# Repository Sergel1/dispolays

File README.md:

# Dispolays - Week 4 Hardware Build

Dispolays is a compact, battery-powered e-paper device built around an ESP32-C3 SuperMini. During Week 4, I designed the custom carrier PCB in KiCad and started a parametric enclosure in SolidWorks.

This is still a **digital prototype**. I did not have the physical components during Week 4, so the PCB footprints, enclosure clearances, charging circuit, and final assembly still need to be checked with the real parts before manufacturing or connecting a LiPo battery.

## What I completed this week

- Designed the complete schematic in KiCad
- Created a custom ESP32-C3 SuperMini symbol and provisional footprint
- Added an MCP73831 LiPo charging circuit
- Added an SS14 battery power path
- Added battery-voltage sensing
- Routed a two-layer PCB with power and signal net classes
- Added GND pours on both copper layers
- Added test points and an antenna keepout
- Exported Gerbers, drill files, and a PCB STEP model
- Imported the PCB into SolidWorks
- Started a parametric PETG enclosure
- Added the display opening, PCB bosses, separator, J2 clearance, side-button slots, and USB-C access

## System overview

The current design includes:

- ESP32-C3 SuperMini mounted on removable 1x8 socket strips
- 1.54-inch, 200x200 black-and-white e-paper display interface
- MCP73831 single-cell LiPo charger
- SS14 Schottky battery power path
- Battery-voltage measurement circuit
- Two side buttons
- Four electrical test points
- Two-layer custom PCB
- Parametric PETG enclosure model

## Schematic

### Main components

- `U1` - ESP32-C3 SuperMini
- `U2` - MCP73831T-2ACI/OT, SOT-23-5, 4.2 V LiPo charger
- `D1` - SS14 Schottky diode, SMA package
- `J1` - 2-pin JST-PH battery connector
- `J2` - 1x8, 2.54 mm e-paper connection header
- `SW1`, `SW2` - side-actuated buttons
- `R1`, `R2` - 1 MOhm battery-voltage divider
- `R3`, `R4` - 100 kOhm external button pull-ups
- `R5` - 5.1 kOhm charger-programming resistor
- `C1`, `C2` - 4.7 uF charger capacitors
- `C3` - 100 nF battery-sense filter capacitor
- `C4` - 100 uF bulk capacitor
- `TP1` - 3V3
- `TP2` - GND
- `TP3` - BAT+
- `TP4` - 5V

### GPIO assignment

| Function | ESP32-C3 pin |
|---|---:|
| VBAT_SENSE | GPIO1 |
| BTN_A | GPIO3 |
| BTN_B | GPIO4 |
| EPD_DC | GPIO5 |
| EPD_SCK | GPIO6 |
| EPD_MOSI | GPIO7 |
| EPD_CS | GPIO10 |
| EPD_BUSY | GPIO20 |
| EPD_RST | GPIO21 |

The following pins are intentionally unused:

```text
GPIO0
GPIO2
GPIO8
GPIO9
```

### E-paper connector pinout

| J2 pin | Signal |
|---:|---|
| 1 | 3V3 |
| 2 | GND |
| 3 | DIN / EPD_MOSI |
| 4 | CLK / EPD_SCK |
| 5 | CS / EPD_CS |
| 6 | DC / EPD_DC |
| 7 | RST / EPD_RST |
| 8 | BUSY / EPD_BUSY |

## Power design

The MCP73831 charge current is set by `R5 = 5.1 kOhm`, giving a target charge current of approximately `196 mA`.

The battery power path is:

```text
BAT+ -> SS14 anode
SS14 cathode -> 5V rail
```

Battery voltage is measured before the diode:

```text
BAT+ -> R1 1 MOhm -> VBAT_SENSE -> R2 1 MOhm -> GND
                              |
                           C3 100 nF
                              |
                             GND
```

## PCB design

The PCB is approximately `38 x 30 x 1.6 mm`, uses two copper layers, and has three mechanical mounting holes.

### Routing choices

- Signal traces: approximately `0.25 mm`
- Power traces: approximately `0.50 mm`
- GND zones on both `F.Cu` and `B.Cu`
- GND stitching vias between both layers
- Antenna rule area blocking copper zones, tracks, and vias
- Current minimum measured antenna clearance: approximately `7.5 mm`

The design target is at least `8 mm`. Because the PCB is now frozen, the enclosure must keep the battery, display cable, screws, and other conductive objects farther away from the antenna region.

### PCB renders

| Front | Back |
|---|---|
|  |  |

## Enclosure design

The enclosure is being designed parametrically in SolidWorks and is intended to be printed in PETG.

### Current Version 1 envelope

```text
Width:  47.0 mm
Height: 88.0 mm
Depth:  21.5 mm
```

### Current enclosure features

- 2.0 mm side walls
- 1.6 mm front wall
- 2.0 mm rear-panel target
- 29 x 29 mm display window
- Upper display and battery zone
- Lower PCB and electronics zone
- Internal separator rib
- Display-cable slot
- Enlarged J2 connector clearance
- Three PCB mounting bosses aligned to the frozen PCB
- Right-side button slots
- Oversized Version 1 USB-C opening
- External USB cable-housing recess
- Back shell started but not yet finished
- Provisional battery pocket still to be completed

The enclosure is being designed around a Waveshare-style 1.54-inch black-and-white e-paper module:

```text
Driver-board outline: 48 x 33 mm
Resolution:           200 x 200
Active area:          approximately 27.6 x 27.6 mm
Interface:            SPI
```

The display is rotated inside the portrait enclosure so its 33 mm dimension runs across the enclosure width.

### Dimensions still waiting for physical parts

- ESP32-C3 SuperMini outline and pin-row spacing
- Socket height and assembled SuperMini stack height
- USB-C connector centre height
- Display thickness and active-area offset
- Display cable and connector size
- Side-switch actuator dimensions
- LiPo size and connector polarity
- C4 height
- Final battery-pocket dimensions

## Repository structure

```text
cad/
├── Dispolays_Enclosure_Assembly.SLDASM
├── Dispolays_Enclosure_Master_front-shell.SLDPRT
└── Dispolays_kicad.step

hardware/
├── Dispolays_week4.kicad_pro
├── Dispolays_week4.kicad_pcb
├── Dispolays_week4_schematics.kicad_sch
├── Dispolays_week4-PTH.drl
└── Dispolays_week4-NPTH.drl

images/
├── Dispolays_schematics.png
├── Enclosure_3D.png
├── Pcb_Editor.png
├── PCB-3d-front.png
└── PCB-3d-back.png
```

The repository also includes the generated fabrication files. Native SolidWorks files should be collected with **Pack and Go** so the assembly does not lose referenced components when opened on another computer.

## Verification completed

- [x] Custom ESP32-C3 SuperMini schematic symbol created
- [x] Custom provisional SuperMini footprint created
- [x] MCP73831 changed to the five-pin SOT-23 package
- [x] Schematic ERC reviewed
- [x] PCB DRC reviewed
- [x] No unconnected nets reported after zone refill
- [x] GND pours added to both copper layers
- [x] Antenna keepout added
- [x] PCB imported into the SolidWorks enclosure assembly
- [x] Three PCB mounting bosses aligned with the PCB mounting holes
- [x] J2 and separator interference identified and cleared
- [x] Side-button openings added
- [x] USB-C access opening added

## Verification still required

### Before PCB ordering

- [ ] Purchase and measure the real ESP32-C3 SuperMini
- [ ] Print the SuperMini footprint at 1:1 scale and test all 16 pins
- [ ] Confirm the selected 1x8 female sockets fit and measure their height
- [ ] Select switches that exactly match the frozen PCB footprints
- [ ] Confirm that the physical display harness fits J2
- [ ] Verify the J1 battery-connector polarity
- [ ] Select the exact protected single-cell LiPo
- [ ] Select a 100 uF capacitor matching the current footprint
- [ ] Complete the back shell and battery pocket
- [ ] Run final enclosure-to-PCB interference checks
- [ ] Export the final enclosure STEP and STL files
- [ ] Inspect Gerbers and drill files in a Gerber viewer

### Before connecting a LiPo

- [ ] Check for shorts between 5V, 3V3, BAT+, and GND
- [ ] Assemble and test without the SuperMini or battery first
- [ ] Apply current-limited 5 V at TP4
- [ ] Confirm that U2 does not overheat
- [ ] Verify that BAT+ is approximately 4.2 V with no battery connected
- [ ] Confirm battery-plug polarity with a multimeter
- [ ] Measure the initial charge current, targeting approximately 196 mA
- [ ] Verify the SS14 power-path voltage drop

### Firmware and breadboard tests

- [ ] T-00: SuperMini identity, sleep current, and wireless test
- [ ] T-01: E-paper full-refresh test
- [ ] T-02: Partial-refresh and ghosting test
- [ ] T-03: Button wake test
- [ ] T-04: Battery ADC test

## Known limitations

1. No physical components were available during Week 4.
2. The SuperMini footprint is provisional and must be verified before fabrication.
3. The enclosure uses conservative Version 1 dimensions and is not yet ready for final printing.
4. The battery, switches, socket strips, display harness, and C4 package have not been physically verified.
5. The PCB uses three mounting holes instead of four.
6. The PCB STEP model does not yet represent the complete removable SuperMini socket stack.

## Safety

This is a custom prototype that includes a single-cell LiPo charging circuit I could have messed something and boom! beware or something 🙏

## Author

**Sergel Hasabella**  
Week 4 hardware design submission

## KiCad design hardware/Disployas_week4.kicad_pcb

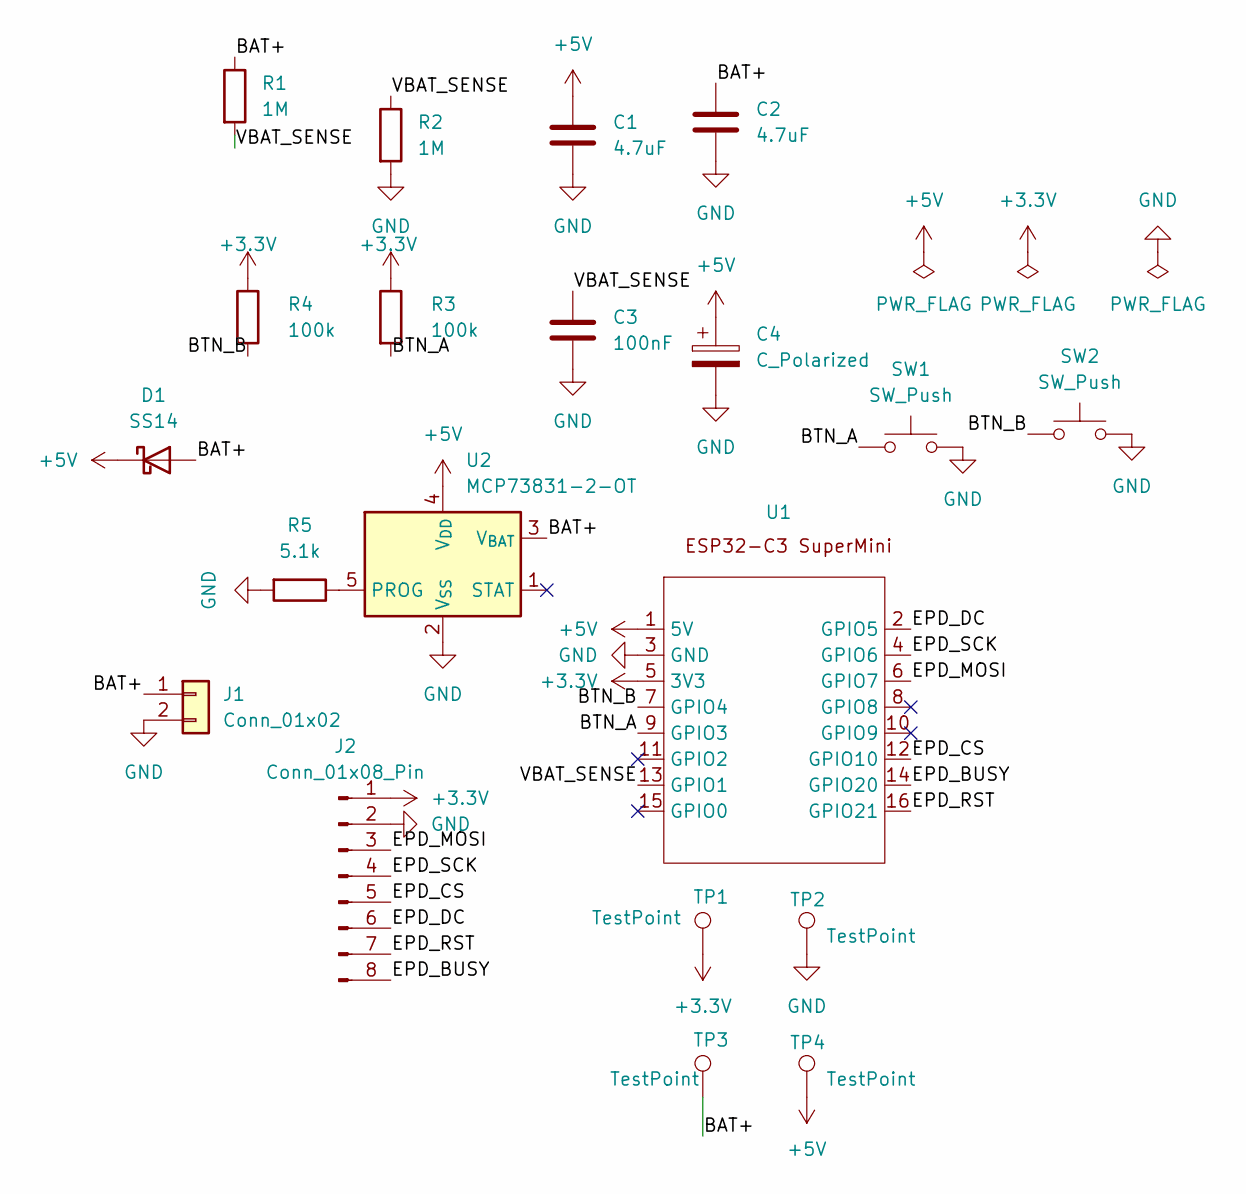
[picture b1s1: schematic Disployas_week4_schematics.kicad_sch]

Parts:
C1, C2: 4.7uF; C_0201_0603Metric
C3: 100nF; C_0201_0603Metric
C4: C_Polarized; CP_Radial_D5.0mm_P2.00mm
D1: SS14; D_SMA
J1: Conn_01x02; JST_PH_B2B-PH-K_1x02_P2.00mm_Vertical
J2: Conn_01x08_Pin; PinHeader_1x08_P2.54mm_Vertical
R1, R2: 1M; C_0201_0603Metric
R3, R4: 100k; C_0201_0603Metric
R5: 5.1k; C_0201_0603Metric
SW1, SW2: SW_Push; SW_SPST_EVQPE1
TP1, TP2, TP3, TP4: TestPoint; TestPoint_Pad_D1.5mm
U1: ESP32-C3_SuperMini_2x08
U2: MCP73831-2-OT; SOT-23-5

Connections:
+3.3V: J2.1, R3.1, R4.1, TP1.1 (1_1), U1.5 (3V3)
+5V: C1.1, C4.1, D1.1 (K), TP4.1 (1_1), U1.1 (5V), U2.4 (V_{DD})
/BAT+: C2.1, D1.2 (A), J1.1, R1.1, TP3.1 (1_1), U2.3 (V_{BAT})
/BTN_A: R3.2, SW1.1, U1.9 (GPIO3)
/BTN_B: R4.2, SW2.1, U1.7 (GPIO4)
/EPD_BUSY: J2.8, U1.14 (GPIO20)
/EPD_CS: J2.5, U1.12 (GPIO10)
/EPD_DC: J2.6, U1.2 (GPIO5)
/EPD_MOSI: J2.3, U1.6 (GPIO7)
/EPD_RST: J2.7, U1.16 (GPIO21)
/EPD_SCK: J2.4, U1.4 (GPIO6)
/VBAT_SENSE: C3.1, R1.2, R2.1, U1.13 (GPIO1)
GND: C1.2, C2.2, C3.2, C4.2, J1.2, J2.2, R2.2, R5.2, SW1.2, SW2.2, TP2.1 (1_1), U1.3 (GND), U2.2 (V_{SS})
unnamed: R5.1, U2.5 (PROG)

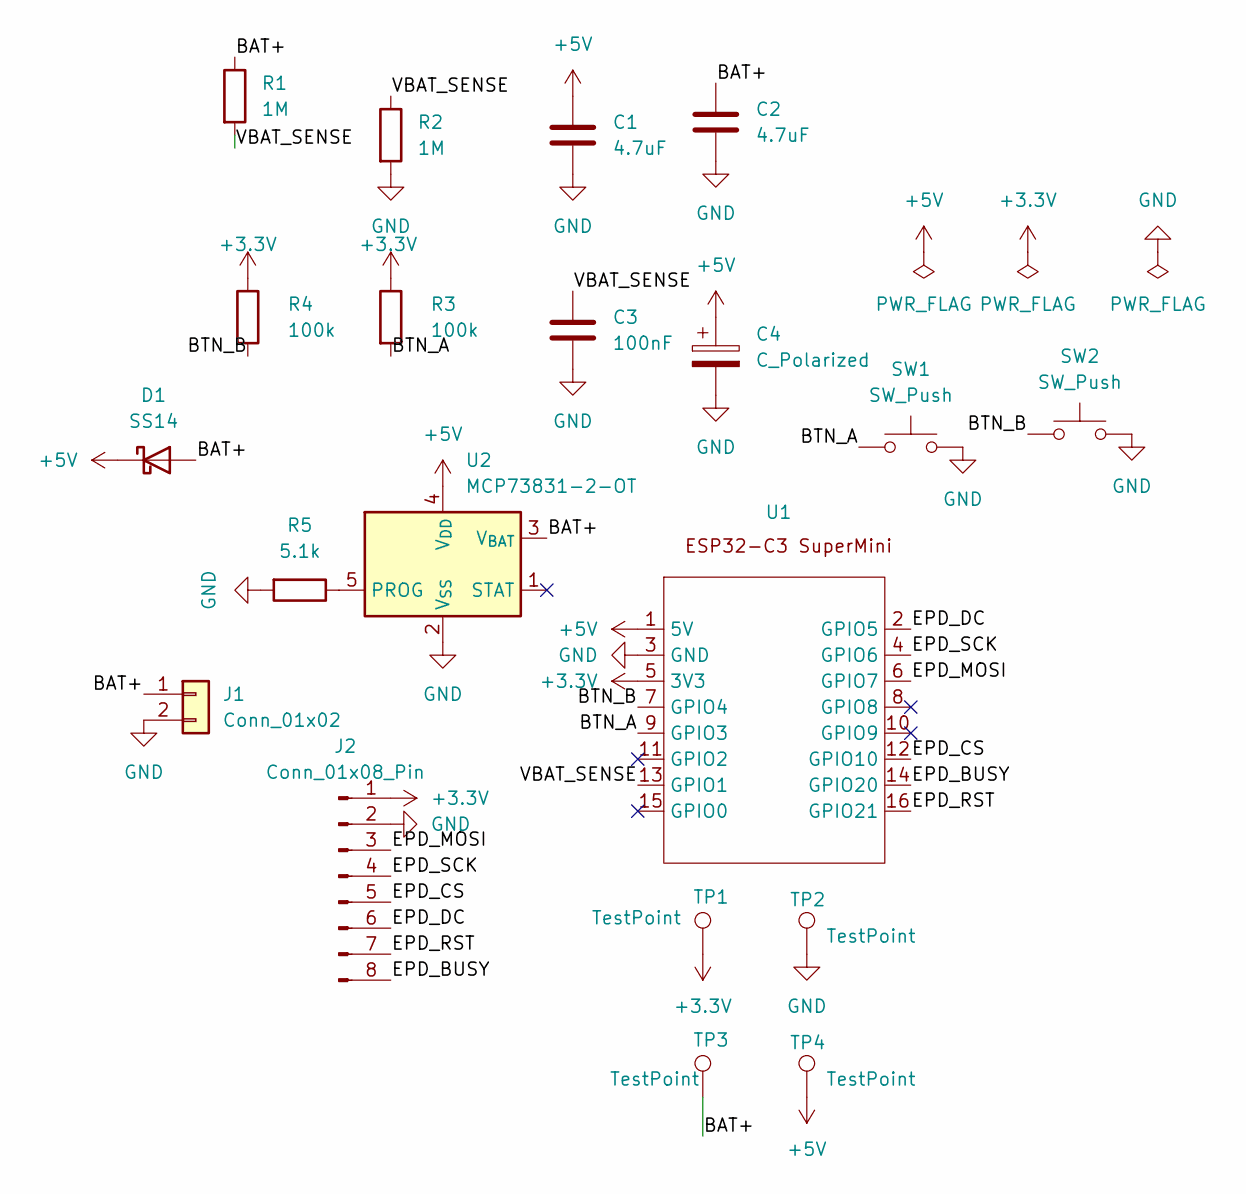
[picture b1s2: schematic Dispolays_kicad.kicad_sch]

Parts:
C1, C2: 4.7uF; C_0201_0603Metric
C3: 100nF; C_0201_0603Metric
C4: C_Polarized; CP_Radial_D5.0mm_P2.00mm
D1: SS14; D_SMA
J1: Conn_01x02; JST_PH_B2B-PH-K_1x02_P2.00mm_Vertical
J2: Conn_01x08_Pin; PinHeader_1x08_P2.54mm_Vertical
R1, R2: 1M; C_0201_0603Metric
R3, R4: 100k; C_0201_0603Metric
R5: 5.1k; C_0201_0603Metric
SW1, SW2: SW_Push; SW_SPST_EVQPE1
TP1, TP2, TP3, TP4: TestPoint; TestPoint_Pad_D1.5mm
U1: ESP32-C3_SuperMini_2x08
U2: MCP73831-2-OT; SOT-23-5

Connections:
+3.3V: J2.1, R3.1, R4.1, TP1.1 (1_1), U1.5 (3V3)
+5V: C1.1, C4.1, D1.1 (K), TP4.1 (1_1), U1.1 (5V), U2.4 (V_{DD})
/BAT+: C2.1, D1.2 (A), J1.1, R1.1, TP3.1 (1_1), U2.3 (V_{BAT})
/BTN_A: R3.2, SW1.1, U1.9 (GPIO3)
/BTN_B: R4.2, SW2.1, U1.7 (GPIO4)
/EPD_BUSY: J2.8, U1.14 (GPIO20)
/EPD_CS: J2.5, U1.12 (GPIO10)
/EPD_DC: J2.6, U1.2 (GPIO5)
/EPD_MOSI: J2.3, U1.6 (GPIO7)
/EPD_RST: J2.7, U1.16 (GPIO21)
/EPD_SCK: J2.4, U1.4 (GPIO6)
/VBAT_SENSE: C3.1, R1.2, R2.1, U1.13 (GPIO1)
GND: C1.2, C2.2, C3.2, C4.2, J1.2, J2.2, R2.2, R5.2, SW1.2, SW2.2, TP2.1 (1_1), U1.3 (GND), U2.2 (V_{SS})
unnamed: R5.1, U2.5 (PROG)

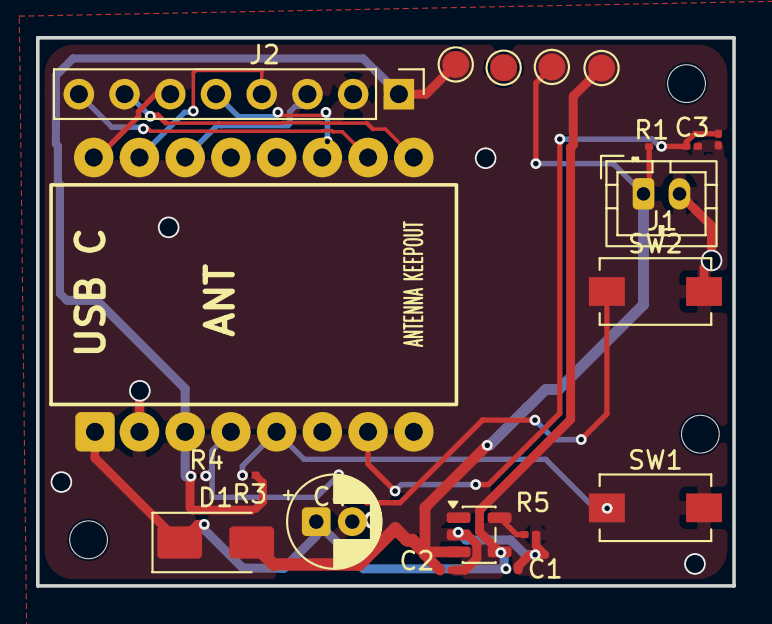
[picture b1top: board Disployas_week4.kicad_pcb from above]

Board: 2 copper layers, 38.7 x 30.5 mm, 20 parts (0 on the bottom side), 14 nets.
